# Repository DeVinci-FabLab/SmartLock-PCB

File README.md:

# SmartLock-PCB

\# SmartLock-PCB

PCB design for the SmartLock project — an electronically controlled lock system developed at the DeVinci FabLab.

Designed with \*\*KiCad\*\*.

\---

\## Project Structure

SmartLock-PCB/

├── SmartLock.kicad\_pro       # KiCad project file

├── SmartLock.kicad\_sch       # Schematic

├── SmartLock.kicad\_pcb       # PCB layout

├── gerbers/                  # Fabrication files (Gerber + drill)

├── bom/                      # Bill of Materials

└── README.md

\## Description

This board handles the control logic for the SmartLock system. It interfaces with:

\- An electronic locking mechanism (solenoid / servo)

\- An access control module (badge reader / keypad / BLE)

\- A microcontroller for logic and communication

>  This section should be updated with the actual components once the schematic is finalized.

\---

\## How to Open the Project

1\. Install \[KiCad](https://www.kicad.org/) (version 7 or later recommended)

2\. Clone this repository:

```

&#x20;  git clone https://github.com/DeVinci-FabLab/SmartLock-PCB.git

```

3\. Open `SmartLock.kicad\_pro` in KiCad

\---

\## Ordering the PCB

Gerber files for fabrication are located in the `gerbers/` folder.  

They can be sent directly to a PCB manufacturer (JLCPCB, PCBWay, etc.).

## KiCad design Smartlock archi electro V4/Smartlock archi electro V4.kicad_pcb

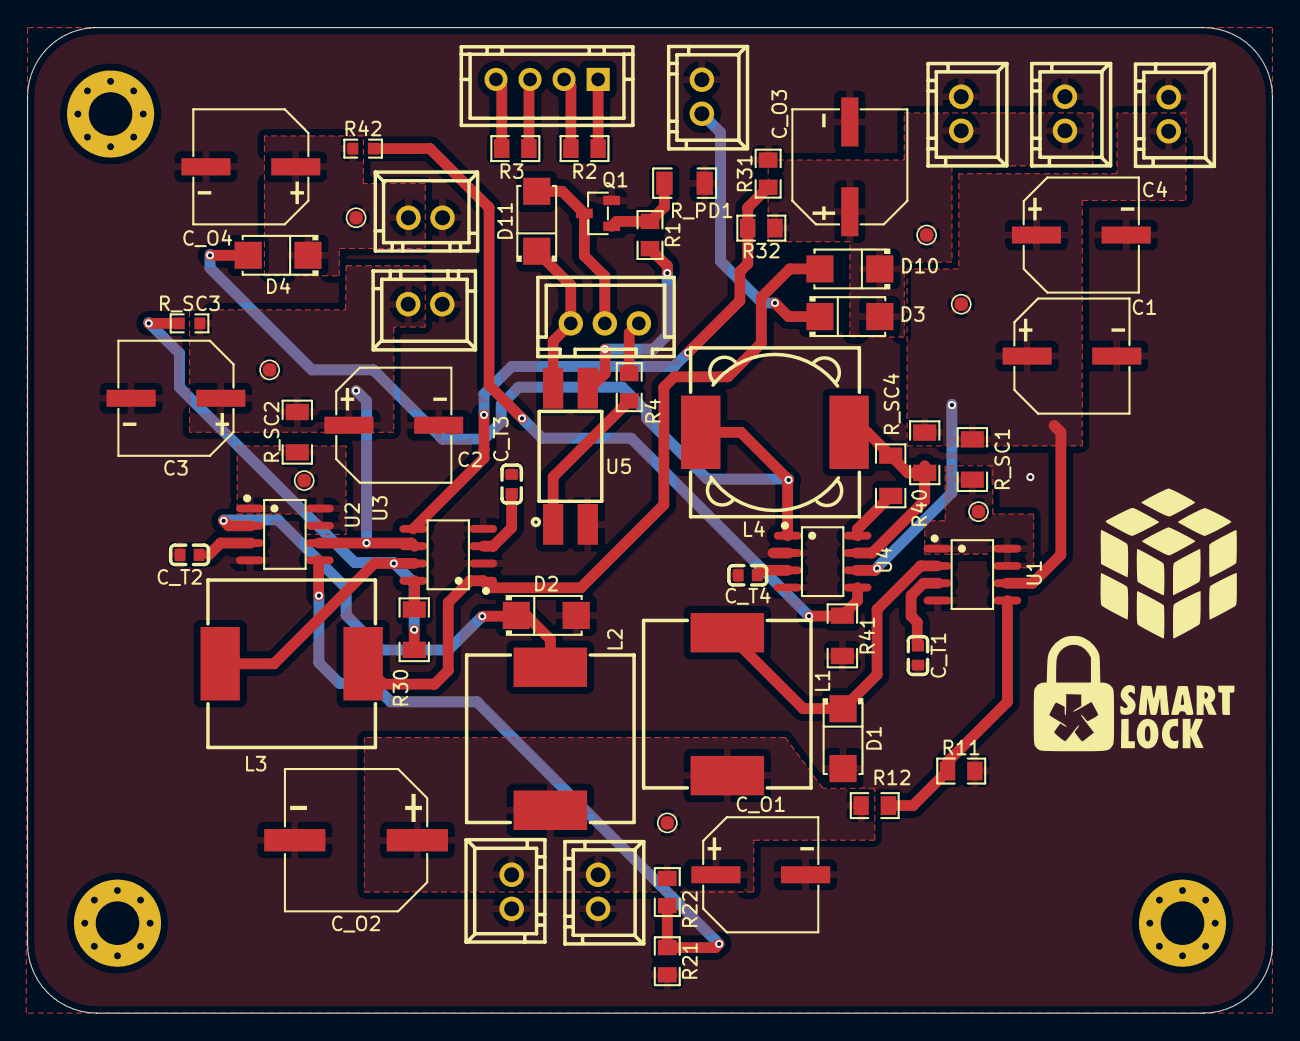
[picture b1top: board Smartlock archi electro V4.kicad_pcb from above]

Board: 2 copper layers, 91.4 x 72.4 mm, 57 parts (0 on the bottom side), 35 nets.

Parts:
C1, C2, C3, C4: C_Polarized; CAP-SMD_BD8.0-L8.3-W8.3-LS9.1-FD
C_O1, C_O3, C_O4: C_Polarized; CAP-SMD_BD8.0-L8.3-W8.3-LS9.1-FD
C_O2: C_Polarized; CAP-SMD_BD10.0-L10.3-W10.3-LS11.3-FD
C_T1, C_T2, C_T3, C_T4: C; C0603
D1, D2, D3, D4, D10, D11: 1N5822; SMA_L4.3-W2.6-LS5.2-RD
L1: L1; IND-SMD_L12.3-W12.3_SMDRI127
L2: L2; IND-SMD_L12.3-W12.3_SMDRI127
L3: L3; IND-SMD_L12.3-W12.3_SMDRI127
L4: L4; IND-SMD_L12.3-W12.3
Q1: Q_NMOS_GSD; SOT-23-3_L2.9-W1.3-P1.90-LS2.4-BR
R1, R2, R3, R4, R11, R12, R21, R22, R31, R32: R; R0805
R30: R30; R1206
R40: R40; R1206
R41: R; R1206
R42: R; R0603
R_PD1: R; R1206
R_SC1, R_SC2, R_SC4: R; R1206
R_SC3: R; R0603
U1: Regulator 12V-5V; SOIC-8_L4.9-W3.9-P1.27-LS6.0-BL
U2: Regulator 11.1V-5V; SOIC-8_L4.9-W3.9-P1.27-LS6.0-BL
U3: Regulator 11.1V-12V; SOIC-8_L4.9-W3.9-P1.27-LS6.0-BL
U4: Regulator 12V-12.6V; SOIC-8_L4.9-W3.9-P1.27-LS6.0-BL
U5: LTV-817; OPTO-SMD-4_L4.6-W6.5-P2.54-LS10.3-BL
U?: CONN-TH_XH-2A
U?#2, U?#3, U?#4, U?#5, U?#6, U?#7, U?#10: CONN-TH_XH-2A
U?#8: CONN-TH_4P-P2.50_XH-4A
U?#9: CONN-TH_XH-3A

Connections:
/Carte_puissance/Regulateur 1 12V-5V/Net-(U1-DC): R_SC1.1, U1.1 (SwC), U1.7 (Ipk), U1.8 (DC)
/Carte_puissance/V_in 12V: C1.1, C4.1, R_SC1.2, R_SC4.2, U1.6 (Vin), U4.6 (Vin), U?#4.2
/Carte_puissance/V_out 5V: C_O1.1, C_O2.1, L1.2, L2.2, R12.1, R22.1, U?#3.1, U?#5.2
/Carte_puissance/V_out 12V: C_O3.1, D3.1 (K), D10.2 (A), R32.1, U?#7.2, U?#10.2
GND: C1.2, C2.2, C3.2, C4.2, C_O1.2, C_O2.2, C_O3.2, C_O4.2, C_T1.2, C_T2.2, C_T3.2, C_T4.2, D1.2 (A), D2.2 (A), Q1.2 (S), R11.2, R21.2, R31.2, R41.2, R_PD1.2, U1.4 (GND), U2.4 (GND), U3.2 (SwE), U3.4 (GND), U4.2 (SwE), U4.4 (GND), U5.2, U?.1, U?#2.1, U?#3.2, U?#4.1, U?#5.1, U?#6.2, U?#7.1, U?#10.1
unnamed: D1.1 (K), L1.1, U1.2 (SwE)
unnamed: D2.1 (K), L2.1, U2.2 (SwE)
unnamed: D3.2 (A), L3.2, U3.1 (SwC)
unnamed: D4.2 (A), L4.2, U4.1 (SwC)
unnamed: D10.1 (K), U?.2
unnamed: D11.2 (A), Q1.3 (D), U?#9.2
unnamed: D11.1 (K), U5.4, U?#9.1
unnamed: R2.1, U?#8.1
unnamed: R3.1, U?#8.3
unnamed: Q1.1 (G), R1.1, R_PD1.1
unnamed: R1.2, U5.3
unnamed: R4.1, U5.1
unnamed: C_T1.1, U1.3 (TC)
unnamed: R11.1, R12.2, U1.5 (Vfb)
unnamed: R_SC2.1, U2.1 (SwC), U2.7 (Ipk), U2.8 (DC)
unnamed: C_T2.1, U2.3 (TC)
unnamed: R21.1, R22.2, U2.5 (Vfb)
unnamed: R30.2, U3.8 (DC)
unnamed: L3.1, R30.1, R_SC3.1, U3.7 (Ipk)
unnamed: C_T3.1, U3.3 (TC)
unnamed: R31.1, R32.2, U3.5 (Vfb)
unnamed: R40.2, U4.8 (DC)
unnamed: L4.1, R40.1, R_SC4.1, U4.7 (Ipk)
unnamed: C_T4.1, U4.3 (TC)
unnamed: R41.1, R42.2, U4.5 (Vfb)
unnamed: R2.2, U?#8.2
unnamed: R3.2, U?#8.4
unnamed: R4.2, U?#9.3
V11.1: C2.1, C3.1, R_SC2.2, R_SC3.2, U2.6 (Vin), U3.6 (Vin), U?#2.2
V12.6: C_O4.1, D4.1 (K), R42.1, U?#6.1

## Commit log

2026-06-06 docs: add minimal README
2026-06-06 add kicad files
